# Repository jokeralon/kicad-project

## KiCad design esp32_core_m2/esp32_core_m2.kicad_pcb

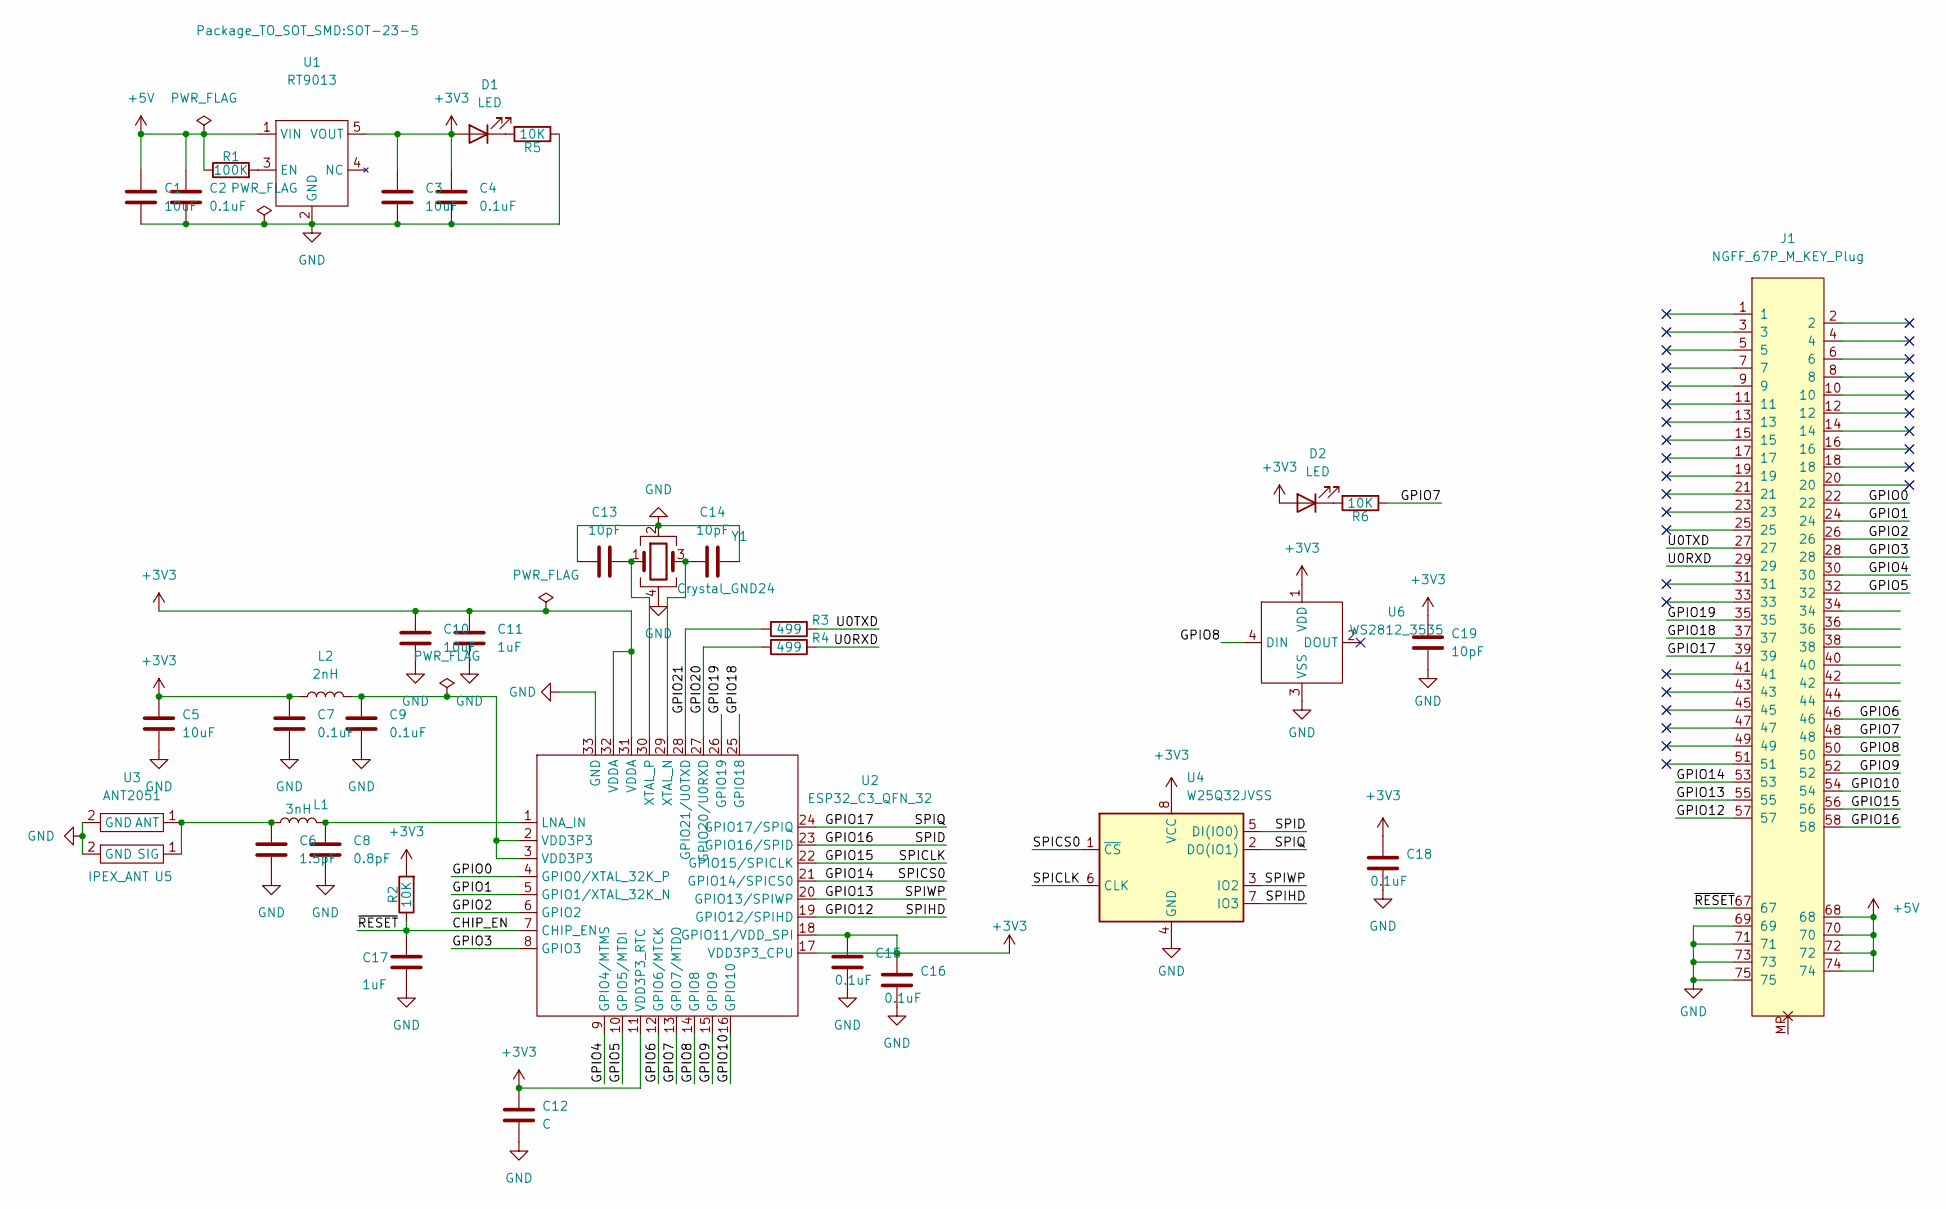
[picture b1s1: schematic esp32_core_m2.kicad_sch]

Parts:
C1, C3, C5, C10: 10uF; C_0402_1005Metric
C2, C4, C7, C9, C15, C16, C18: 0.1uF; C_0402_1005Metric
C6: 1.5pF; C_0402_1005Metric
C8: 0.8pF; C_0402_1005Metric
C11, C17: 1uF; C_0402_1005Metric
C12: C; C_0402_1005Metric
C13, C14, C19: 10pF; C_0402_1005Metric
D1, D2: LED; LED_0603_1608Metric
J1: NGFF_67P_M_KEY_Plug; NGFF_2230_67P_P0.5_M_KEY_Plug_复制(copy)
L1: 3nH; R_0402_1005Metric
L2: 2nH; R_0402_1005Metric
R1: 100K; R_0402_1005Metric
R2, R5, R6: 10K; R_0402_1005Metric
R3, R4: 499; R_0402_1005Metric
U1: RT9013; SOT-23-5
U2: ESP32_C3_QFN_32; QFN-32-1EP_5x5mm_P0.5mm_EP3.1x3.1mm_ThermalVias
U3: ANT2051; ANT_2051
U4: W25Q32JVSS; SOIC-8_5.23x5.23mm_P1.27mm
U5: IPEX_ANT
U6: WS2812_3535; LED_SMT_4P_3535
Y1: Crystal_GND24; Crystal_SMD_3225-4Pin_3.2x2.5mm

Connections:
+3V3: C3.1, C4.1, C5.2, C7.2, C10.2, C11.2, C12.1, C15.1, C16.1, C18.1, C19.2, D1.2 (A), D2.2 (A), L2.1, R2.2, U1.5 (VOUT), U2.11 (VDD3P3_RTC), U2.17 (VDD3P3_CPU), U2.18 (GPIO11/VDD_SPI), U2.31 (VDDA), U2.32 (VDDA), U4.8 (VCC), U6.1 (VDD)
+5V: C1.1, C2.1, J1.68, J1.70, J1.72, J1.74, R1.1, U1.1 (VIN)
/CHIP_EN: C17.2, J1.67, R2.1, U2.7 (CHIP_EN)
/GPIO0: J1.22, U2.4 (GPIO0/XTAL_32K_P)
/GPIO1: J1.24, U2.5 (GPIO1/XTAL_32K_N)
/GPIO2: J1.26, U2.6 (GPIO2)
/GPIO3: J1.28, U2.8 (GPIO3)
/GPIO4: J1.30, U2.9 (GPIO4/MTMS)
/GPIO5: J1.32, U2.10 (GPIO5/MTDI)
/GPIO6: J1.46, U2.12 (GPIO6/MTCK)
/GPIO7: J1.48, R6.1, U2.13 (GPIO7/MTDO)
/GPIO8: J1.50, U2.14 (GPIO8), U6.4 (DIN)
/GPIO9: J1.52, U2.15 (GPIO9)
/GPIO10: J1.54, U2.16 (GPIO10)
/GPIO12: J1.57, U2.19 (GPIO12/SPIHD), U4.7 (IO3)
/GPIO13: J1.55, U2.20 (GPIO13/SPIWP), U4.3 (IO2)
/GPIO14: J1.53, U2.21 (GPIO14/SPICS0), U4.1 (~CS)
/GPIO15: J1.56, U2.22 (GPIO15/SPICLK), U4.6 (CLK)
/GPIO16: J1.58, U2.23 (GPIO16/SPID), U4.5 (DI(IO0))
/GPIO17: J1.39, U2.24 (GPIO17/SPIQ), U4.2 (DO(IO1))
/GPIO18: J1.37, U2.25 (GPIO18)
/GPIO19: J1.35, U2.26 (GPIO19)
/GPIO20: R4.2, U2.27 (GPIO20/U0RXD)
/GPIO21: R3.2, U2.28 (GPIO21/U0TXD)
/U0RXD: J1.29, R4.1
/U0TXD: J1.27, R3.1
GND: C1.2, C2.2, C3.2, C4.2, C5.1, C6.1, C7.1, C8.2, C9.2, C10.1, C11.1, C12.2, C13.2, C14.2, C15.2, C16.2, C17.1, C18.2, C19.1, J1.69, J1.71, J1.73, J1.75, R5.1, U1.2 (GND), U2.33 (GND), U3.2 (GND), U4.4 (GND), U5.2 (GND), U6.3 (VSS), Y1.2, Y1.4
unnamed: C6.2, L1.1, U3.1 (ANT), U5.1 (SIG)
unnamed: C8.1, L1.2, U2.1 (LNA_IN)
unnamed: C9.1, L2.2, U2.2 (VDD3P3), U2.3 (VDD3P3)
unnamed: C13.1, U2.30 (XTAL_P), Y1.1
unnamed: C14.1, U2.29 (XTAL_N), Y1.3
unnamed: D1.1 (K), R5.2
unnamed: D2.1 (K), R6.2
unnamed: R1.2, U1.3 (EN)

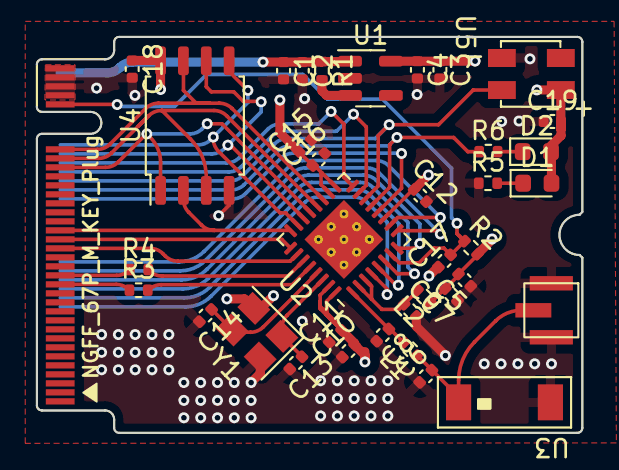
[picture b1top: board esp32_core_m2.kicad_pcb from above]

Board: 4 copper layers, 30.3 x 22.0 mm, 37 parts (0 on the bottom side), 35 nets.

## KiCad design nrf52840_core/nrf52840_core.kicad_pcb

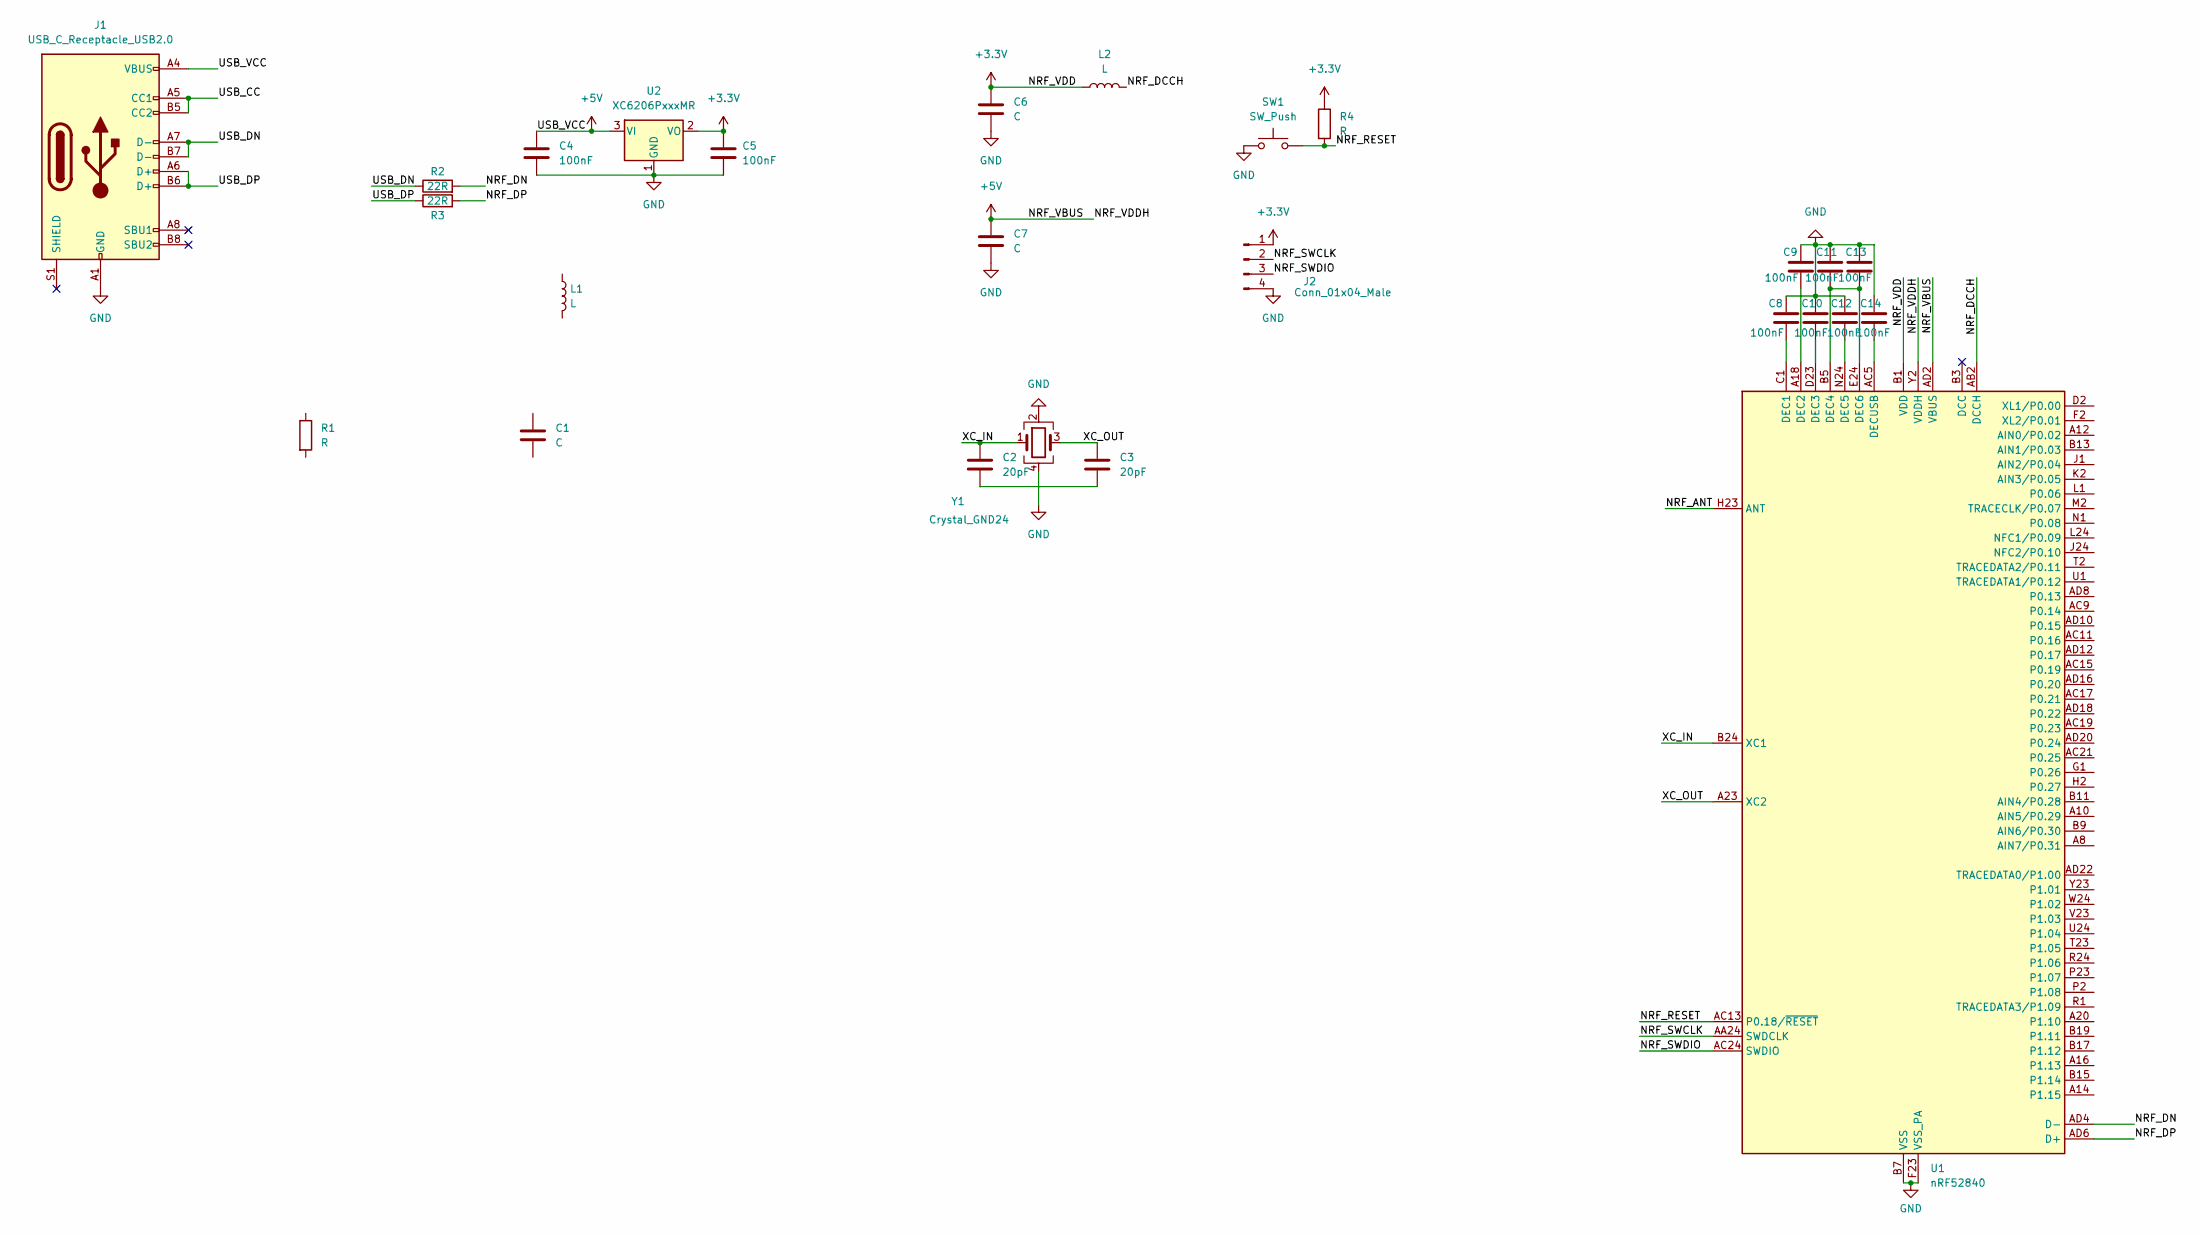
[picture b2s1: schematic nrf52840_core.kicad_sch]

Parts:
C1, C6, C7: C; C_0603_1608Metric
C2, C3: 20pF; C_0603_1608Metric
C4, C5, C8, C9, C10, C11, C12, C13, C14: 100nF; C_0603_1608Metric
J1: USB_C_Receptacle_USB2.0; USB_C_Receptacle_HRO_TYPE-C-31-M-12
J2: Conn_01x04_Male; PinHeader_1x04_P2.54mm_Vertical
L1, L2: L; L_0603_1608Metric
R1, R4: R; R_0603_1608Metric
R2, R3: 22R; R_0603_1608Metric
SW1: SW_Push; SW_DIP_SPSTx01_Slide_6.7x4.1mm_W6.73mm_P2.54mm_LowProfile_J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
U1: nRF52840; Nordic_AQFN-73-1EP_7x7mm_P0.5mm
U2: XC6206PxxxMR; SOT-23
Y1: Crystal_GND24; Crystal_SMD_SeikoEpson_FA238-4Pin_3.2x2.5mm

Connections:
+3.3V: C5.1, C6.1, J2.1, L2.1, R4.1, U1.A22 (VDD), U1.AD14 (VDD), U1.AD23 (VDD), U1.B1 (VDD), U1.W1 (VDD), U2.2 (VO)
+5V: C4.1, C7.1, J1.A4 (VBUS), J1.A9 (VBUS), J1.B4 (VBUS), J1.B9 (VBUS), U1.AD2 (VBUS), U1.Y2 (VDDH), U2.3 (VI)
/NRF_ANT: U1.H23 (ANT)
/NRF_DCCH: L2.2, U1.AB2 (DCCH)
/NRF_DN: R2.2, U1.AD4 (D-)
/NRF_DP: R3.2, U1.AD6 (D+)
/NRF_RESET: R4.2, SW1.2, U1.AC13 (P0.18/~RESET)
/NRF_SWCLK: J2.2, U1.AA24 (SWDCLK)
/NRF_SWDIO: J2.3, U1.AC24 (SWDIO)
/USB_CC: J1.A5 (CC1), J1.B5 (CC2)
/USB_DN: J1.A7 (D-), J1.B7 (D-), R2.1
/USB_DP: J1.A6 (D+), J1.B6 (D+), R3.1
/XC_IN: C2.1, U1.B24 (XC1), Y1.1
/XC_OUT: C3.1, U1.A23 (XC2), Y1.3
GND: C4.2, C5.2, C6.2, C7.2, C8.1, C9.1, C10.1, C11.1, C12.1, C13.1, C14.1, J1.A1 (GND), J1.A12 (GND), J1.B1 (GND), J1.B12 (GND), J2.4, SW1.1, U1.B7 (VSS), U1.EP (VSS), U1.F23 (VSS_PA), U2.1 (GND), Y1.2, Y1.4
unnamed: C2.2, C3.2
unnamed: C9.2, U1.A18 (DEC2)
unnamed: C14.2, U1.AC5 (DECUSB)
unnamed: C11.2, C13.2, U1.B5 (DEC4), U1.E24 (DEC6)
unnamed: C8.2, U1.C1 (DEC1)
unnamed: C10.2, U1.D23 (DEC3)
unnamed: C12.2, U1.N24 (DEC5)

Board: 2 copper layers, 26 parts (0 on the bottom side), 21 nets, no tracks yet.

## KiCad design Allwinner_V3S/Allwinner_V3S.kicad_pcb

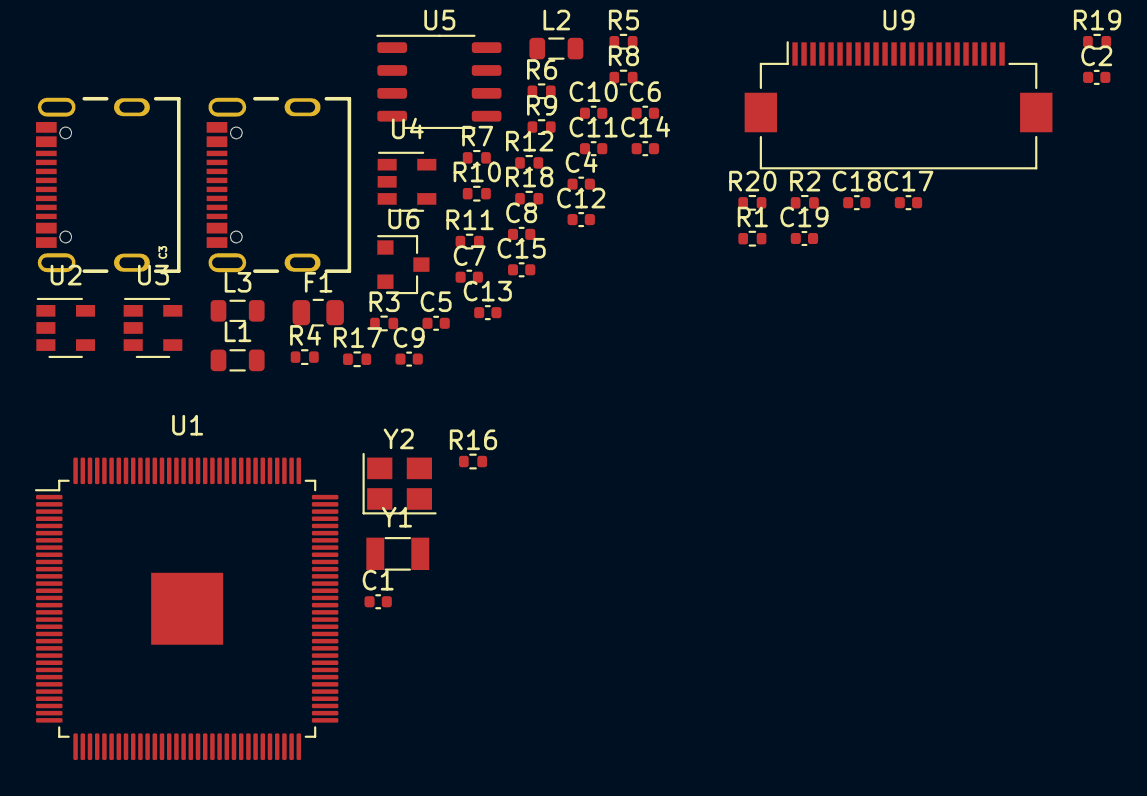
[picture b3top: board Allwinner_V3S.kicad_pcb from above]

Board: 2 copper layers, 49 parts (0 on the bottom side), 47 nets, no tracks yet.

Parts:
C1: 10uF; C_0402_1005Metric
C2, C12, C14, C17, C18, C19: 104; C_0402_1005Metric
C3, C16: USB-TypeC-16Pin; USB-TYPT-C-16PIN
C4, C5, C6, C7, C8, C9, C10, C11, C13, C15: 106; C_0402_1005Metric
F1: Fuse; Fuse_0805_2012Metric
L1, L2, L3: 2.2uH; L_0805_2012Metric
R1, R2: 10K; R_0402_1005Metric
R3, R4, R11, R12, R17, R18: 22; R_0402_1005Metric
R5, R6, R7, R10: 150K; R_0402_1005Metric
R8: 680K; R_0402_1005Metric
R9: 300K; R_0402_1005Metric
R16: 240; R_0402_1005Metric
R19, R20: 0/NC; R_0402_1005Metric
U1: Allwinner_V3S; ELQFP-129_14x14mm_P0.4mm
U2, U3, U4: SY8088AAC; SOT-23-5
U5: CH340N; SOP-8_3.9x4.9mm_P1.27mm
U6: XC6206PxxxMR; SOT-23
U9: OV7724_FPC_24PIN; Hirose_FH12-24S-0.5SH_1x24-1MP_P0.50mm_Horizontal
Y1: 32.768K; Crystal_SMD_3215-2Pin_3.2x1.5mm
Y2: 24M; Crystal_SMD_3225-4Pin_3.2x2.5mm

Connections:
+1V2: C9.1, C9.2, L3.2, R10.1, U1.19, U1.20, U1.21, U1.25, U1.26, U1.38, U1.47, U1.51, U1.56, U1.58, U1.64, U1.80, U1.88, U1.108, U1.126
+1V8: C8.1, C8.2, C17.1, L2.2, R9.1, R19.2, U1.59, U1.60, U1.61, U1.62, U1.65, U1.66, U1.67, U1.68, U1.69, U1.70, U1.72, U1.79, U9.10
+3V0: C14.1, C15.1, U1.115, U6.2
+3V3: C2.1, C7.1, C7.2, C18.1, L1.2, R1.2, R8.1, R20.2, U1.12, U1.29, U1.50, U1.57, U1.76, U1.85, U1.98, U1.104, U1.109, U1.122, U1.127, U9.4, U9.24
+5V: C4.1, C5.1, C6.1, C10.1, C12.1, C13.1, F1.1, U2.1, U2.4, U3.1, U3.4, U4.1, U4.4, U5.5, U6.3
/camera/OV7725_HREF: U1.35, U9.9
/camera/OV7725_MCLK: U1.36, U9.13
/camera/OV7725_PCLK: U1.37, U9.17
/camera/OV7725_PWDN: R2.2, U9.8
/camera/OV7725_RESET: R1.1, U9.6
/camera/OV7725_SIO-C: U1.9, U9.5
/camera/OV7725_SIO-D: U1.8, U9.3
/camera/OV7725_VSYNC: U1.34, U9.7
/camera/OV7725_Y2: U1.28, U9.19
/camera/OV7725_Y3: U1.27, U9.21
/camera/OV7725_Y4: U1.24, U9.22
/camera/OV7725_Y5: U1.23, U9.20
/camera/OV7725_Y6: U1.22, U9.18
/camera/OV7725_Y7: U1.18, U9.16
/camera/OV7725_Y8: U1.17, U9.14
/camera/OV7725_Y9: U1.16, U9.12
/power/USB0_DN: C3.A7, C3.B7, R4.2
/power/USB0_DP: C3.A6, C3.B6, R3.2
/power/USB1_DN: C16.A7, C16.B7, R18.1, R18.2, U1.110
/power/USB1_DP: C16.A6, C16.B6, R17.1, R17.2, U1.111
/power/VBUS: C3.A4_B9, C3.B4_A9, C16.A4_B9, C16.B4_A9, F1.2
/v3s_core/DRAM_VREF: U1.63, U1.71
/v3s_core/PB8_TWI1_SCK_UART0_TX_PB_EINT8: R11.1, U1.48
/v3s_core/PB9_TWI1_SDA_UART0_RX_PB_EINT9: R12.1, U1.49
GND: C1.2, C2.2, C3.A1_B12, C3.B1_A12, C4.2, C5.2, C6.2, C10.2, C11.1, C12.2, C13.2, C14.2, C15.2, C16.A1_B12, C16.B1_A12, C17.2, C18.2, C19.2, R2.1, R5.2, R6.2, R7.2, R16.2, U1.116, U1.129, U2.2, U3.2, U4.2, U5.3, U6.1, U9.2, U9.15, U9.23, Y2.2, Y2.4
unnamed: C1.1, U1.97
unnamed: C11.2, U5.8
unnamed: C19.1, R19.1, R20.1, U9.11
unnamed: L1.1, U2.3
unnamed: L2.1, U3.3
unnamed: L3.1, U4.3
unnamed: R3.1, U5.1
unnamed: R4.1, U5.2
unnamed: R5.1, R8.2, U2.5
unnamed: R6.1, R9.2, U3.5
unnamed: R7.1, R10.2, U4.5
unnamed: R11.2, U5.7
unnamed: R12.2, U5.6
unnamed: R16.1, U1.73
unnamed: U1.74, Y2.1
unnamed: U1.75, Y2.3
unnamed: U1.96, Y1.1

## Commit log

2022-09-26 esp32_core_m2
